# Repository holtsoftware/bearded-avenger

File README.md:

bearded-avenger
===============

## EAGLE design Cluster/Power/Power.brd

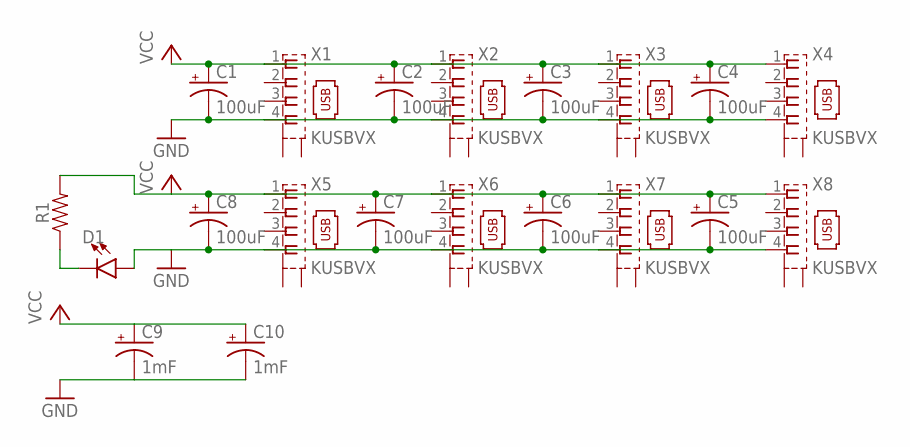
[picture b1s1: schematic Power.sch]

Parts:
C1, C2, C3, C4, C5, C6, C7, C8: 100uF; CPOL-RADIAL-2.5MM-6.5MM
C9, C10: 1mF; CPOL-RADIAL-5MM-10MM
D1: LED3MM; LED_3MM
R1: AXIAL-0.3
X1, X2, X3, X4, X5, X6, X7, X8: KUSBVX

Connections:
GND: C1.2 (-), C2.2 (-), C3.2 (-), C4.2 (-), C5.2 (-), C6.2 (-), C7.2 (-), C8.2 (-), C9.-, C10.-, D1.A, X1.4, X2.4, X3.4, X4.4, X5.4, X6.4, X7.4, X8.4
unnamed: D1.K (C), R1.P$1 (1)
VCC: C1.1 (+), C2.1 (+), C3.1 (+), C4.1 (+), C5.1 (+), C6.1 (+), C7.1 (+), C8.1 (+), C9.+, C10.+, R1.P$2 (2), X1.1, X2.1, X3.1, X4.1, X5.1, X6.1, X7.1, X8.1

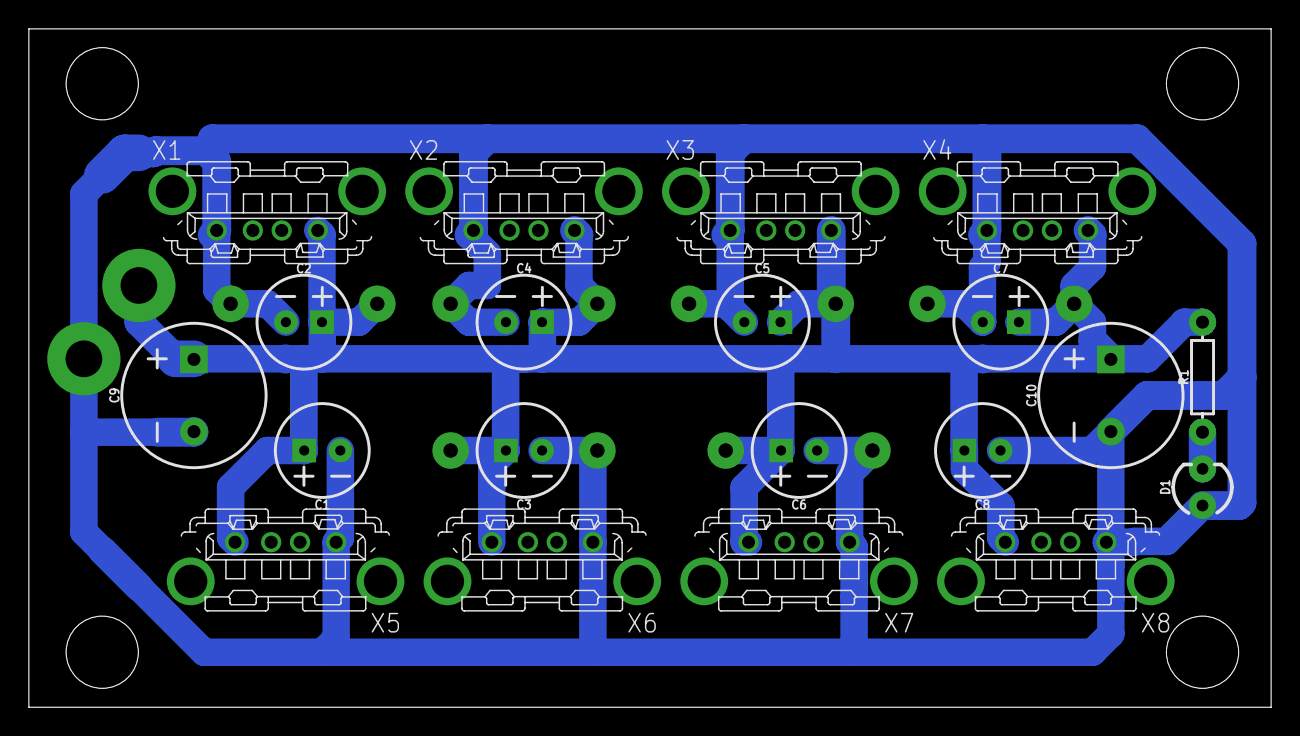
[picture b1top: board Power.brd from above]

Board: 2 copper layers, 86.0 x 47.0 mm, 20 parts (0 on the bottom side), 3 nets.

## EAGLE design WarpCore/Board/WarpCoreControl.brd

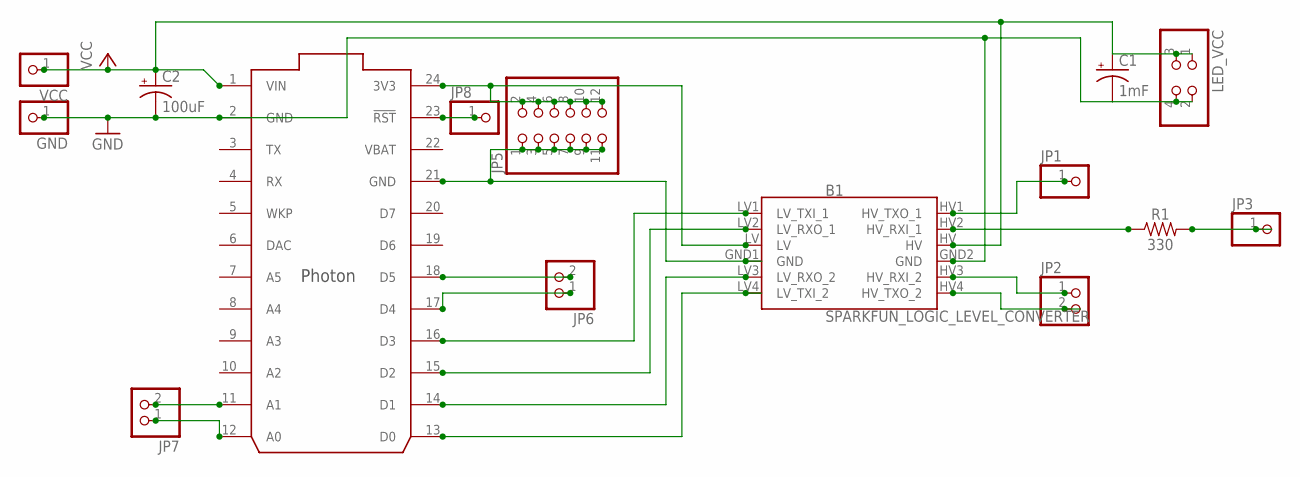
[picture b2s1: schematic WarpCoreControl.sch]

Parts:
B1: SPARKFUN_LOGIC_LEVEL_CONVERTER
C1: 1mF; CPOL-RADIAL-5MM-10MM
C2: 100uF; CPOL-RADIAL-2.5MM-6.5MM
GND: PINHD-1X1; 1X01
JP1, JP3, JP8: PINHD-1X1; 1X01
JP2, JP6, JP7: PINHD-1X2; 1X02
JP5: PINHD-2X6; 2X06
LED_VCC: PINHD-2X2; 2X02
R1: 330; AXIAL-0.3
U$1: PHOTON_WITH_HEADERS; PHOTON
VCC: PINHD-1X1; 1X01

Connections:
3V3: B1.LV, JP5.2, JP5.4, JP5.6, JP5.8, JP5.10, JP5.12, U$1.24 (3V3)
A0: JP7.1, U$1.12 (A0)
A1: JP7.2, U$1.11 (A1)
D0: B1.LV4 (LV_TXI_2), U$1.13 (D0)
D1: B1.LV3 (LV_RXO_2), U$1.14 (D1)
D2: B1.LV2 (LV_RXO_1), U$1.15 (D2)
D3: B1.LV1 (LV_TXI_1), U$1.16 (D3)
D4: JP6.1, U$1.17 (D4)
D5: JP6.2, U$1.18 (D5)
GND: B1.GND1 (GND), B1.GND2 (GND), C1.-, C2.2 (-), GND.1, JP5.1, JP5.3, JP5.5, JP5.7, JP5.9, JP5.11, LED_VCC.2, LED_VCC.4, U$1.2 (GND), U$1.21 (GND)
HAD2: JP3.1, R1.P$2 (2)
HD0: B1.HV4 (HV_TXO_2), JP2.2
HD1: B1.HV3 (HV_RXI_2), JP2.1
HD2: B1.HV2 (HV_RXI_1), R1.P$1 (1)
HD3: B1.HV1 (HV_TXO_1), JP1.1
RST: JP8.1, U$1.23 (!RST)
VBAT: U$1.22 (VBAT)
VCC: B1.HV, C1.+, C2.1 (+), LED_VCC.1, LED_VCC.3, U$1.1 (VIN), VCC.1

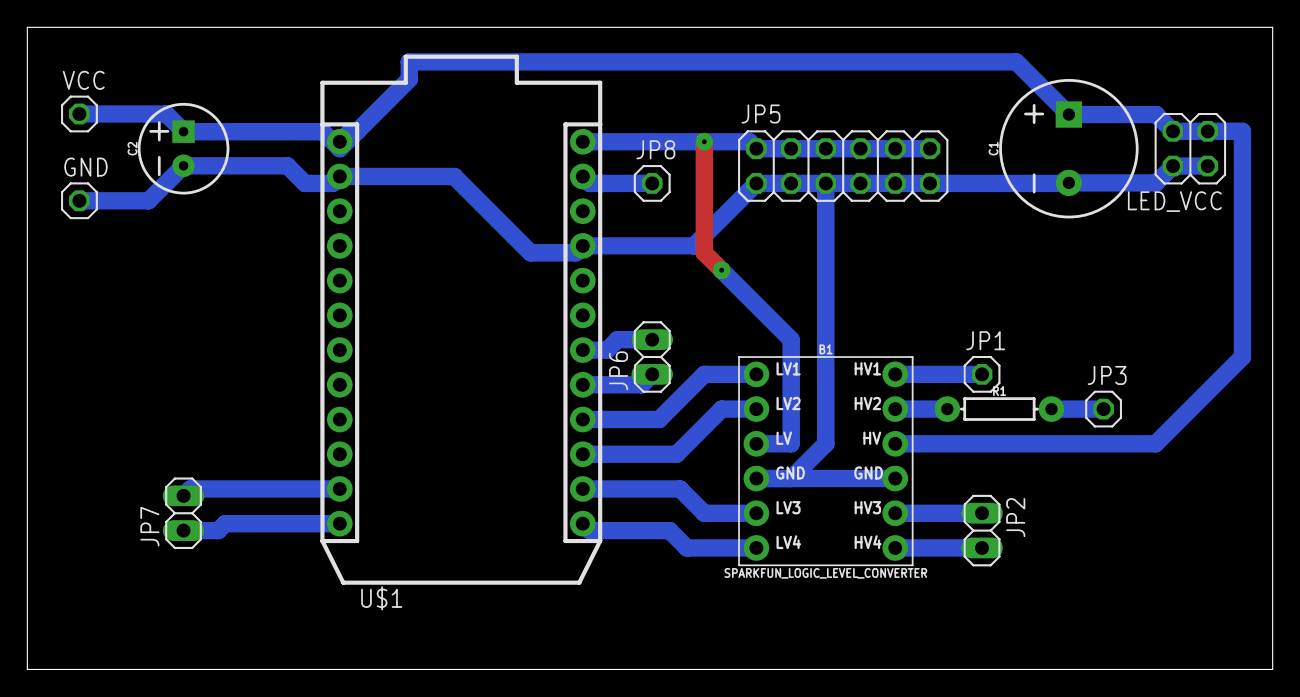
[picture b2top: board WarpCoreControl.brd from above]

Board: 2 copper layers, 91.1 x 47.0 mm, 15 parts (0 on the bottom side), 17 nets.

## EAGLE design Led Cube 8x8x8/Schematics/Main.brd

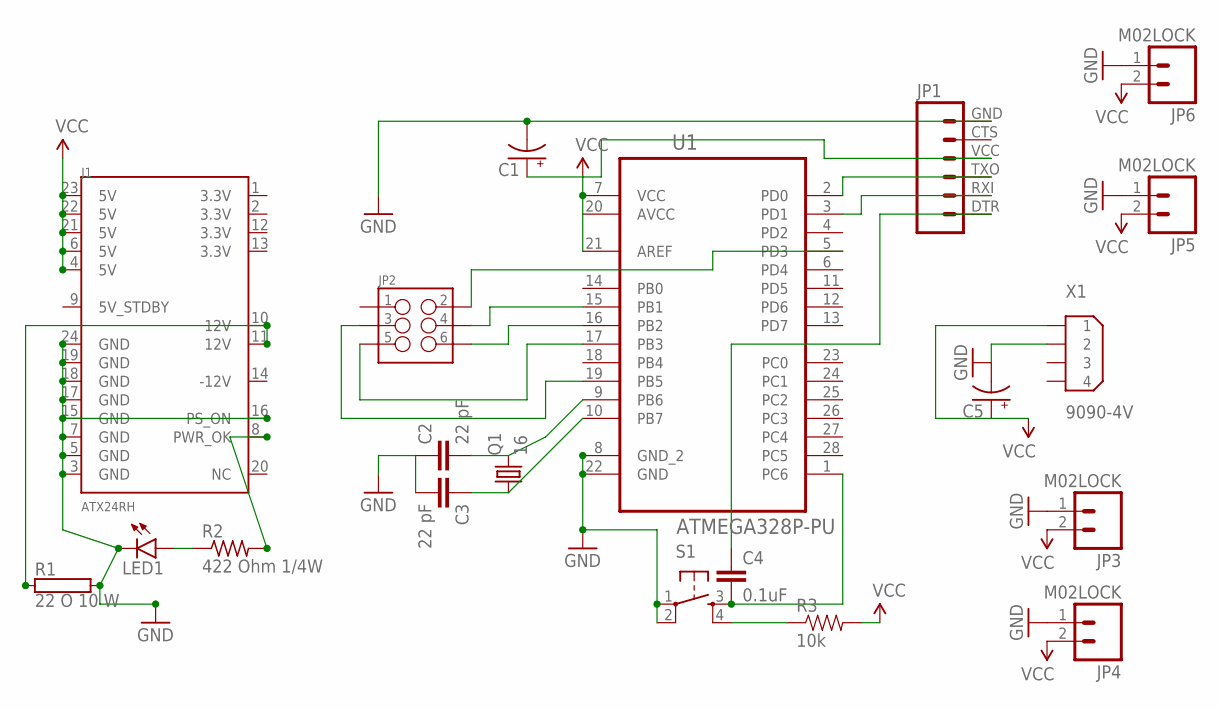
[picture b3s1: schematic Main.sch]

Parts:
C1, C5: CAP_POLPTH2; CPOL-RADIAL-10UF-25V
C2, C3: 22 pF; C2.5-3
C4: 0.1uF; 0603-CAP
J1: ATX24RH; ATX24_RIGHT_ANGLE
JP1: M06SIP; 1X06
JP2: M03X22X3_SILK_SM; 2X3
JP3, JP4, JP5, JP6: M02LOCK; 1X02_LOCK
LED1: LED0603; LED-0603
Q1: 16; HC49/S
R1: 22 O 10 W; RWM8X45
R2: 422 Ohm 1/4W; M3216
R3: 10k; AXIAL-0.3
S1: TAC_SWITCHPTH; TACTILE-PTH
U1: ATMEGA328P-PU; DIP254P762X457-28
X1: 9090-4V

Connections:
GND: C1.2 (-), C2.1, C3.2, C5.2 (-), J1.3 (GND), J1.5 (GND), J1.7 (GND), J1.15 (GND), J1.16 (PS_ON), J1.17 (GND), J1.18 (GND), J1.19 (GND), J1.24 (GND), JP1.GND (6), JP3.1, JP4.1, JP5.1, JP6.1, LED1.C, R1.2, S1.1, S1.2, U1.8 (GND_2), U1.22 (GND), X1.2
unnamed: C4.2, S1.3, U1.1 (PC6)
unnamed: J1.10 (12V), J1.11 (12V), R1.1
unnamed: LED1.A, R2.1
unnamed: J1.8 (PWR_OK), R2.2
unnamed: R3.P$1 (1), S1.4
unnamed: C2.2, Q1.2, U1.9 (PB6)
unnamed: C3.1, Q1.1, U1.10 (PB7)
unnamed: JP1.TXO (3), U1.2 (PD0)
unnamed: JP1.RXI (2), U1.3 (PD1)
unnamed: C4.1, JP1.DTR (1)
unnamed: JP2.3, U1.19 (PB5)
unnamed: JP2.5, U1.17 (PB3)
unnamed: JP2.6, U1.16 (PB2)
unnamed: JP2.4, U1.15 (PB1)
unnamed: JP2.2, U1.5 (PD3)
VCC: C1.1 (+), C5.1 (+), J1.4 (5V), J1.6 (5V), J1.21 (5V), J1.22 (5V), J1.23 (5V), JP1.VCC (4), JP3.2, JP4.2, JP5.2, JP6.2, R3.P$2 (2), U1.7 (VCC), U1.20 (AVCC), U1.21 (AREF), X1.1

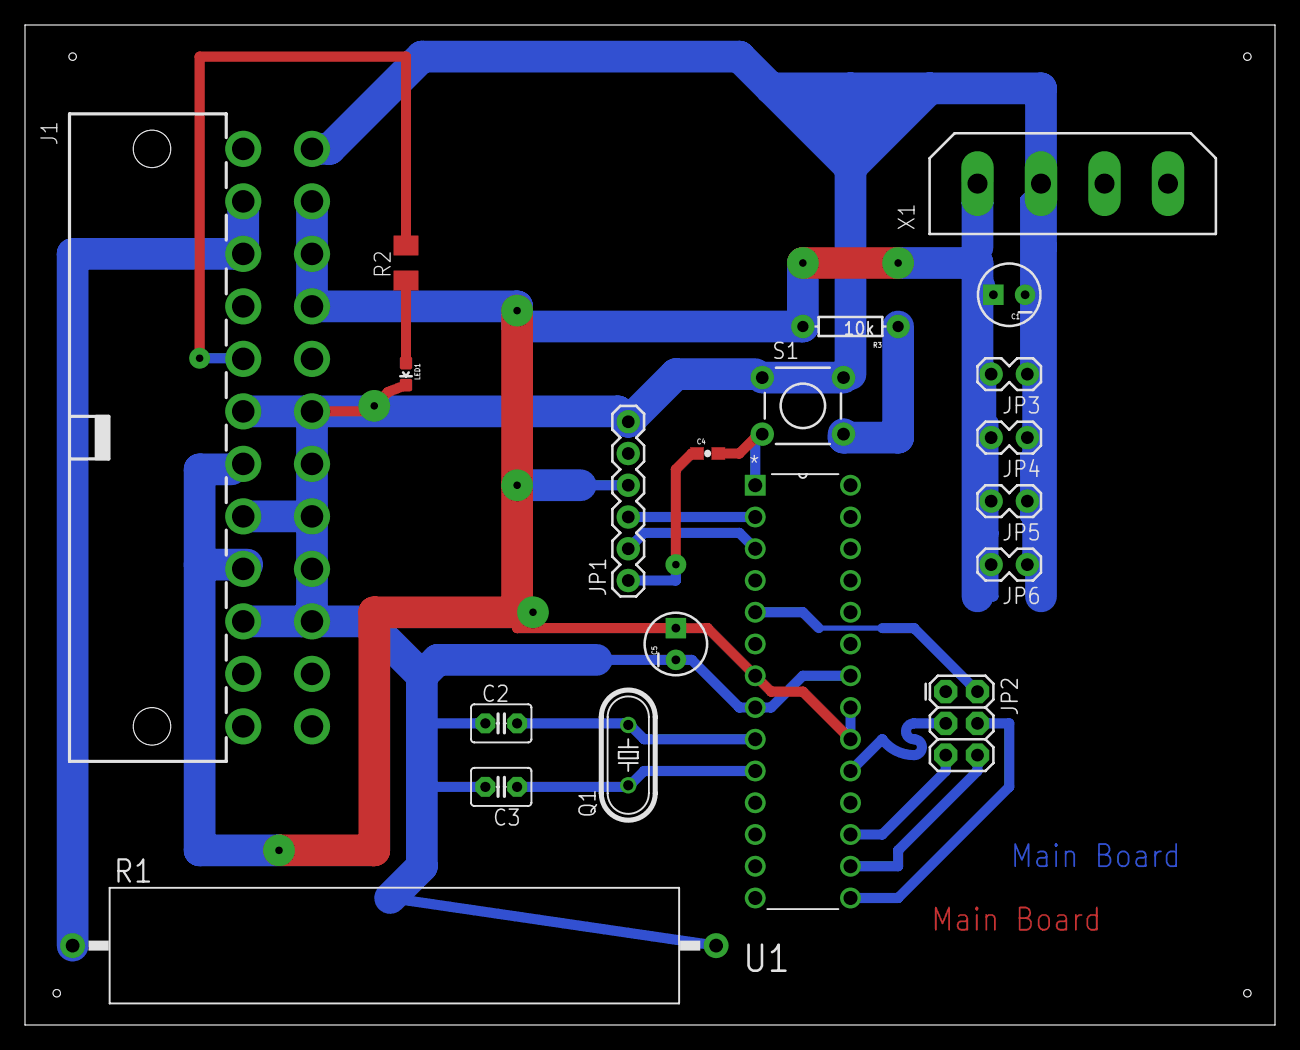
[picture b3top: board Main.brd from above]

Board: 2 copper layers, 100.0 x 80.0 mm, 20 parts (0 on the bottom side), 17 nets.

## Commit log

2014-08-08 Added Start of main Board
2014-08-12 Added Missing Files
2014-08-12 Files.
2015-02-05 A Few changes.
2015-03-03 FRMR
2015-06-28 added cupholderinsert and Rail case
2015-09-06 added more models
2015-09-20 added Code for Joey's lamp and some models
2015-09-30 Added uncommited items.
2015-10-09 Added ShutOffPower Program Code
2015-10-09 Added Files
2016-10-24 Added TalkingWall
2016-10-25 Updated credentials cache
2016-10-25 updated cert
2017-06-12 Added CurtonHook. Talkingwall ios
2017-11-16 Rebuild of Speaker Mount
2017-11-23 Added Center Mount
2017-12-30 added light supports
2018-01-11 added some more parts
2018-01-29 Progress
2018-01-30 Progress on code for WarpCore
2018-05-28 Finalized some objects.
2018-12-16 Added holder
2018-12-21 Updated WarpCore
2022-06-22 Bump Newtonsoft.Json in /TalkingWall/TalkingWall/TalkingWall.Droid
    Bumps [Newtonsoft.Json](https://github.com/JamesNK/Newtonsoft.Json) from 8.0.3 to 13.0.1.
    - [Release notes](https://github.com/JamesNK/Newtonsoft.Json/releases)
    - [Commits](https://github.com/JamesNK/Newtonsoft.Json/compare/8.0.3...13.0.1)
    ---
    updated-dependencies:
    - dependency-name: Newtonsoft.Json
2022-06-22 Bump Newtonsoft.Json in /TalkingWall/TalkingWall/TalkingWall.iOS
    Bumps [Newtonsoft.Json](https://github.com/JamesNK/Newtonsoft.Json) from 8.0.3 to 13.0.1.
    - [Release notes](https://github.com/JamesNK/Newtonsoft.Json/releases)
    - [Commits](https://github.com/JamesNK/Newtonsoft.Json/compare/8.0.3...13.0.1)
    ---
    updated-dependencies:
    - dependency-name: Newtonsoft.Json
2022-06-22 Bump Newtonsoft.Json in /TalkingWall/TalkingWall/TalkingWall.Windows
    Bumps [Newtonsoft.Json](https://github.com/JamesNK/Newtonsoft.Json) from 8.0.3 to 13.0.1.
    - [Release notes](https://github.com/JamesNK/Newtonsoft.Json/releases)
    - [Commits](https://github.com/JamesNK/Newtonsoft.Json/compare/8.0.3...13.0.1)
    ---
    updated-dependencies:
    - dependency-name: Newtonsoft.Json
2022-06-22 Bump Newtonsoft.Json in /TalkingWall/TalkingWall/TalkingWall.WinPhone
    Bumps [Newtonsoft.Json](https://github.com/JamesNK/Newtonsoft.Json) from 8.0.3 to 13.0.1.
    - [Release notes](https://github.com/JamesNK/Newtonsoft.Json/releases)
    - [Commits](https://github.com/JamesNK/Newtonsoft.Json/compare/8.0.3...13.0.1)
    ---
    updated-dependencies:
    - dependency-name: Newtonsoft.Json
2023-12-18 stuff
2024-11-24 lots of updates

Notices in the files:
parts and their libraries:
SparkFun-Capacitors: Licensing: Creative Commons ShareAlike 4.0 International - https://creativecommons.org/licenses/by-sa/4.0
